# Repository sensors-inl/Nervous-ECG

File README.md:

<p align="center">
    <h1 align="center">Nervous ECG Sensor</h1>
</p>

<p align="center">

</p>

## Table of Contents

- [Table of Contents](#table-of-contents)
- [Overview](#overview)
- [Features](#features)
- [Instructions](#instructions)
- [Releases](#releases)
- [Contributing](#contributing)
- [License](#license)
- [Acknowledgments](#acknowledgments)
- [Contact](#contact)

---

## Overview

The **Nervous** project is an initiative based on open-hardware and open-source principles, aimed at providing wearable sensors and software for analyzing the Autonomic Nervous System (ANS) activity.

The **Nervous ECG** project is part of the **[Nervous Toolkit](https://github.com/sensors-inl/Nervous-Toolkit)** and includes hardware design files and firmware source files for creating an electrocardiogram (ECG) sensor to measure the ECG signal **from the hands or forearms**.
The device is wireless and transmits the collected data via Bluetooth Low Energy.

---

## Features

This project is actually a collection of three sub-projects for the sensor design, located in the following directories:

[hardware](./hardware/): This folder contains ECAD files for producing PCBs and assembling circuits for a wireless wrist-worn ECG sensor.
A archive (.zip) containing the design and manufacturing/assembly files for the sensor is available in the releases of this project.

[firmware](./firmware/): This folder contains source files to build binaries for programming the microcontroller.
Precompiled binaries are also provided in the releases of this project.

[web-app](./web-app/): While the sensor is primarily designed to work with the [```nervous-sensors```](https://github.com/sensors-inl/Nervous-Sensors) Python package included in the Nervous Toolkit, a standalone web application is provided for simplified use of the sensor.
It offers sensor control, real-time data visualization, and recording features.
Pre-built executables for both Microsoft Windows and Linux are also available in the releases of this project.

---

## Instructions

Detailed instructions are provided in each subdirectory for manufacturing, programming, and using the sensor.

---

## Releases

Each [release](https://github.com/sensors-inl/Nervous-ECG/releases/latest) contains built firmware and application binaries as well as an archive of ECAD files.

---

## Contributing

Contributions are what make the open-source community such a great place to learn, inspire, and create. Any contributions you make are greatly appreciated. You can open an issue to report a bug, request a feature, or submit a pull request.

---

## License

This project, along with the entire Nervous initiative, is licensed under the [MIT License](https://opensource.org/licenses/MIT). For more details, see the [License](LICENSE.md) file.

---

## Acknowledgments

The main contributors to this project are Bertrand Massot, Matthieu Mesnage, and Hugo Buy from INSA Lyon, CNRS, INL UMR 5270, Villeurbanne, France.

This work was supported by the **French National Research Agency (ANR)** under grant **ANR-22-CE31-0023-03 RENFORCE**.

---

## Contact

[bertrand.massot@insa-lyon.fr](mailto:bertrand.massot@insa-lyon.fr)

---

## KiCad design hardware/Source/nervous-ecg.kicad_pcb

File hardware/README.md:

<p align="center">
    <h1 align="center">Nervous ECG Hardware</h1>
</p>

<p align="center">

</p>

## Table of Contents

- [Table of Contents](#table-of-contents)
- [Overview](#overview)
- [Hardware features](#hardware-features)
- [Manufacturing and assembling](#manufacturing-and-assembling)
  - [PCB properties for manufacturing](#pcb-properties-for-manufacturing)
- [Modification](#modification)
- [Casing](#casing)
- [Note on cables and electrodes placement to reduce signal noise](#note-on-cables-and-electrodes-placement-to-reduce-signal-noise)
- [Release](#release)

---

## Overview

This folder contains ECAD files for the production of PCBs and assembly of circuits for the Nervous ECG sensor.
The printed circuit board was designed using the open source electronics design automation suite [KiCad EDA](https://www.kicad.org/) v9.0.0

Originally designed for measuring heart rate via electrodes placed on the forearms or hands, this sensor utilizes the AD8232 along with passive components, as described in the "EXERCISE APPLICATION: HEART RATE MEASURED AT THE HANDS" section on page 27 of the [datasheet](<https://www.analog.com/media/en/technical-documentation/data-sheets/ad8232.pdf>).
You can modify this configuration for different applications and electrode placements.

The microcontroller used is the nRF52840 (Nordic Semiconductor) within the ISP1807 System-in-Package (Insight SiP).

---

## Hardware features

- USB-C connector for charging the battery
- Embedded LiPo battery charger and I2C fuel gauge
- On/Off SPST button (enables/disables the voltage regulator)
- RGB status LED
- AD8232 ECG AFE with a 7 Hz - 24 Hz bandpass filter (56 dB @ 13 Hz) and RLD
- nRF52840 (ISP1807) with Bluetooth Low Energy

---

## Manufacturing and assembling

The following files are available in the `Export` folder:

- **Export/Manufacturing**: contains Gerber (.gbr) and drill files (.drl)
- **Export/Assembly**: contains assembly drawing (.pdf), pick and place files (.pos), and BOM (.csv)

---

### PCB properties for manufacturing

Some PCB manufacturers may require the following properties. The table below summarizes the principal PCB properties:

| Property                    | Value              |
| --------------------------- | ------------------ |
| Dimensions                  | 21.5 mm x 33.5 mm  |
| Number of layers            | 2                  |
| Minimal insulation width    | 0.150 mm           |
| Minimal trace width         | 0.150 mm           |
| Minimal hole size           | 0.200 mm           |

---

## Modification

The `Source` folder contains the original KiCad project, created using KiCad version 7.0.8.

---

## Casing

Several 3D models are available for producing a casing for the electronics. STEP and STL files are located in the `Casing` folder:

- **casing_top** and **casing_bottom** are two parts that assemble together with two M2 screws, where the PCB and a 150 mAh LiPo battery fit. A specially designed battery compartment ensures that it does not overlap with the antenna of the ISAP1807 chip located on the longitudinal edge of the PCB. The design of the bottom part includes handles for wrist attachment.
- **casing_bottom_controller** is a modified version of the bottom part, designed to mount the electronics circuit and battery onto a Valve Index controller for ECG assessment during virtual environment sessions.

---

## Note on cables and electrodes placement to reduce signal noise

This sensor is designed to capture ECG signals under various conditions while minimizing discomfort. To achieve this, it uses high gain to support electrode placement on the hands or forearms, where signal strength is typically lower. However, this placement also amplifies sensitivity to motion artifacts, which can affect heart rate accuracy.

To minimize these artifacts, we recommend using solid gel electrodes, such as the 3M&reg; 2650. The sensor features a simple 2.54 mm, 3-way header for custom electrode connections. It is recommended to use short cables for the two electrodes near the device (RLD and RA), and a longer cable for the third electrode on the opposite arm (LA). The cables are designed with female crimp terminals at the sensor end and snap adapters at the electrode end. We recommend using cables with low triboelectric effect, such as Belden 9239 Low Noise Coaxial cable. To reduce noise from connector friction, securely hold the electrodes and cables near the electrodes with medical tape.

---

## Release

The entire folder is provided as an archive (`Nervous-ECG-hardware-vX.X.X.zip`) in the [releases](https://github.com/sensors-inl/Nervous-ECG/releases/latest) of this project.

---

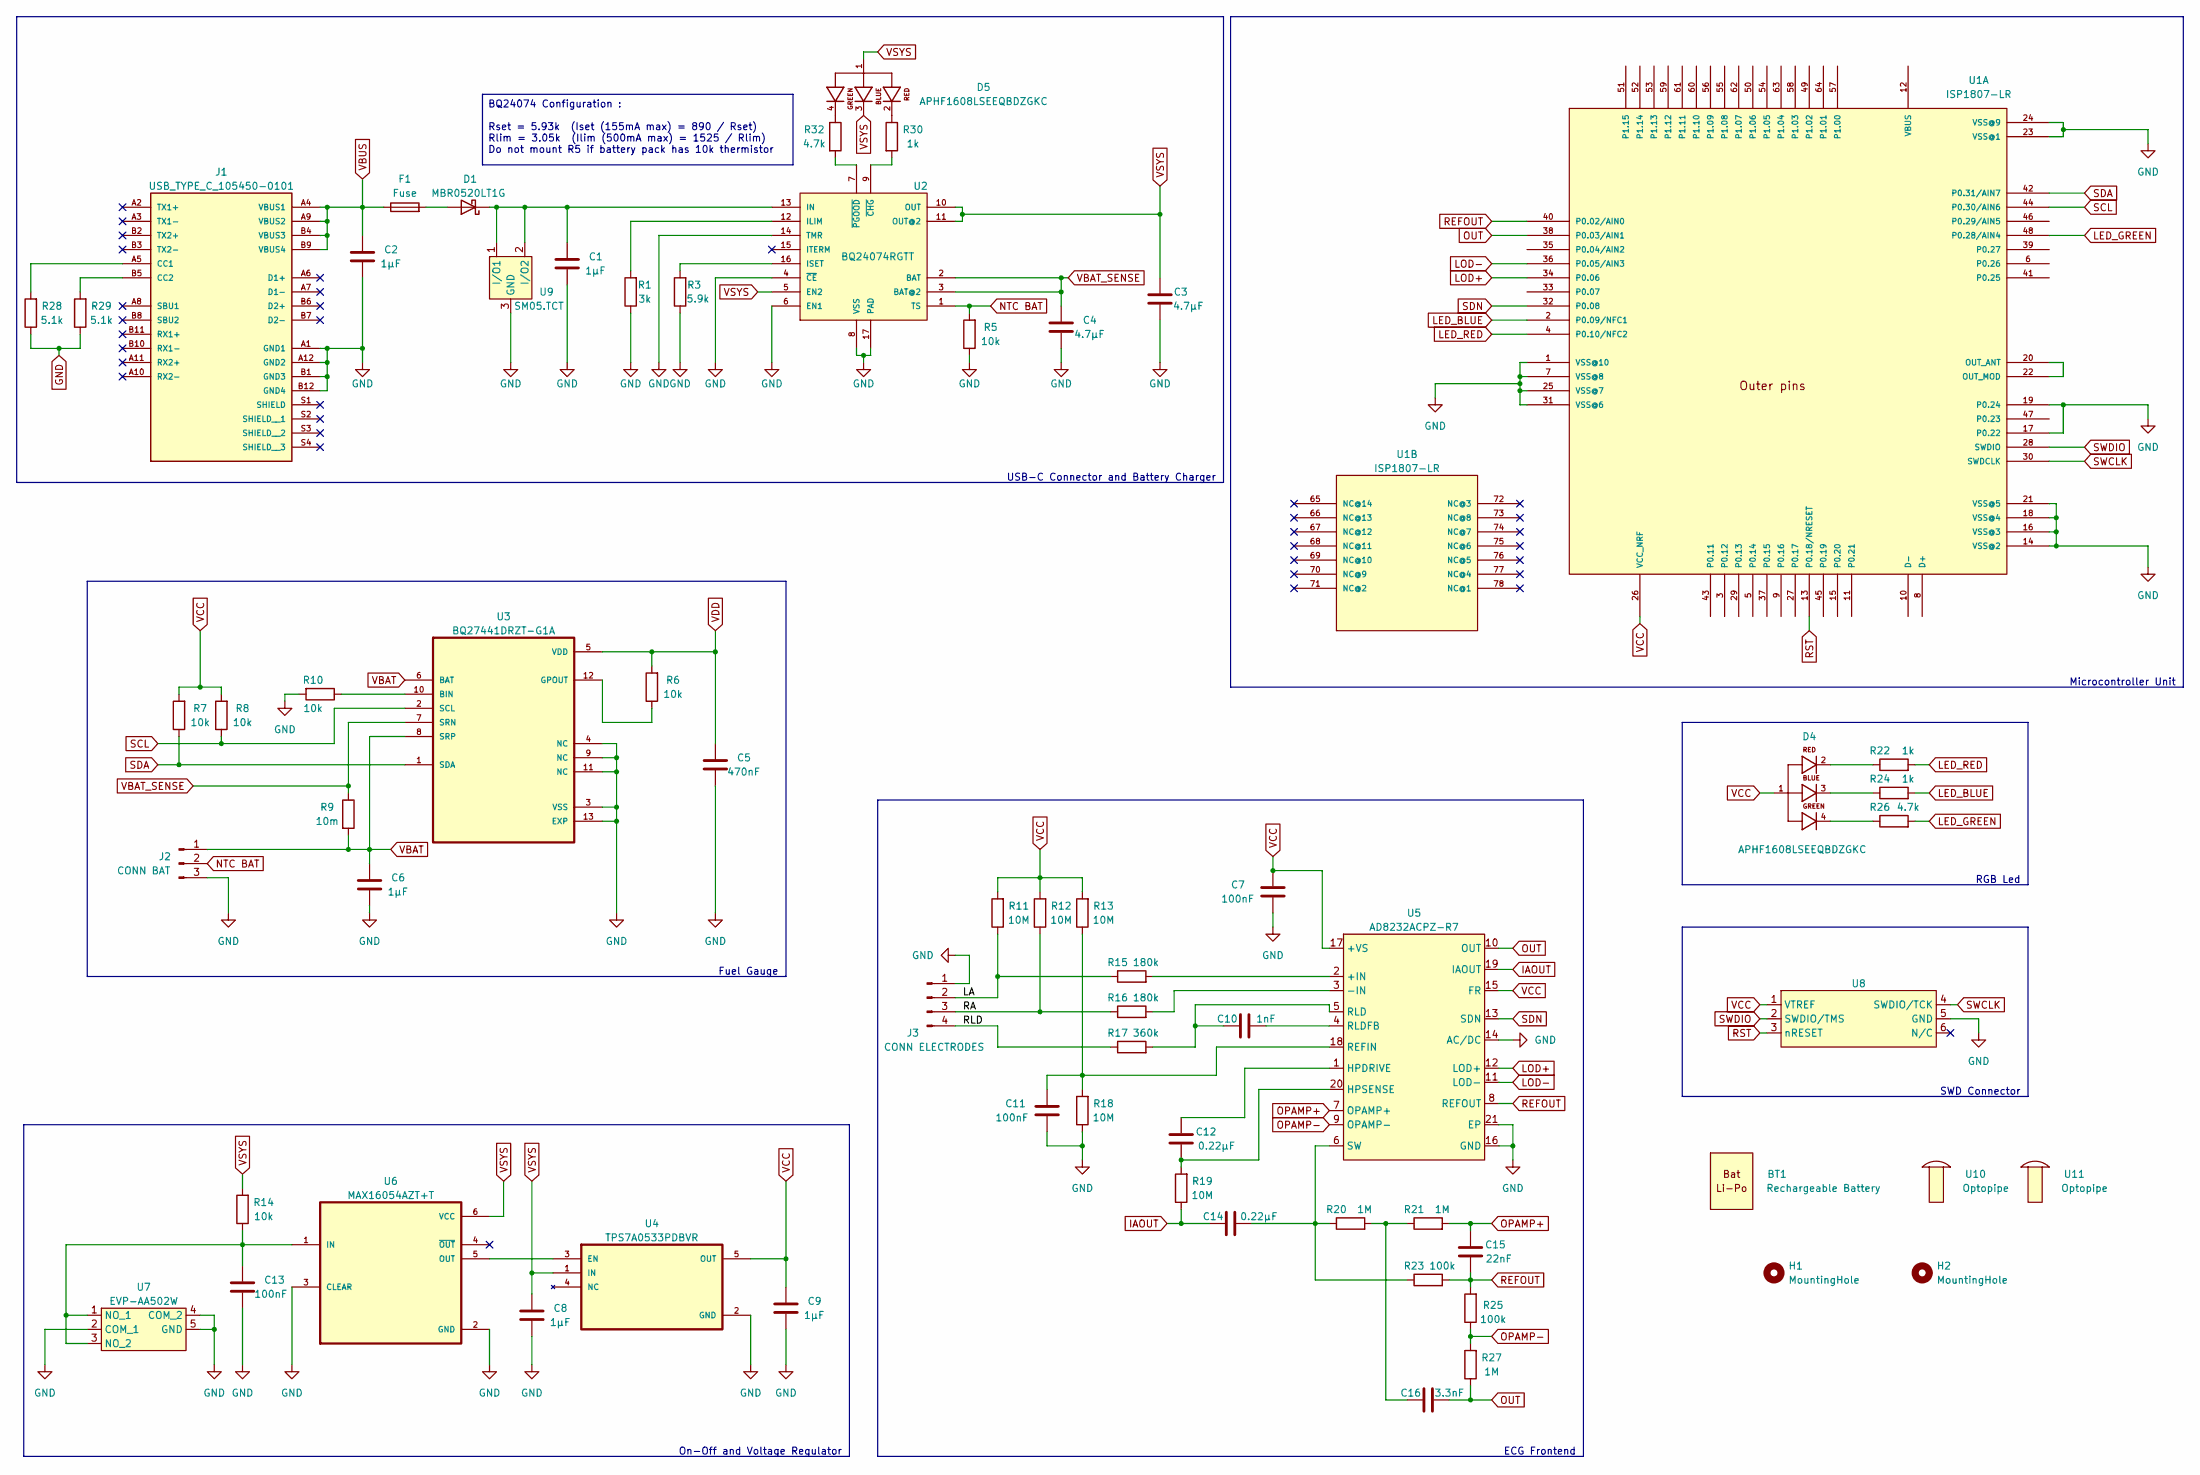
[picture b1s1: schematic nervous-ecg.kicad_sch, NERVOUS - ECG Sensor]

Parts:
BT1: BATT LI-PO 3.7V 165MAH; Manufacturer Part Number LP-402025-1S-3
C1, C2, C6, C8, C9: CAP CER 1UF 10V X5R 0402; C_0402_1005Metric; Manufacturer Part Number CC0402KRX5R6BB105
C3, C4: CAP CER 4.7UF 6.3V X5R 0402; C_0402_1005Metric; Manufacturer Part Number CC0402KRX5R5BB475
C5: CAP CER 0.47UF 10V X5R 0402; C_0402_1005Metric; Manufacturer Part Number CC0402KRX5R6BB474
C7, C11, C13: CAP CER 0.1UF 16V X7R 0402; C_0402_1005Metric; Manufacturer Part Number CC0402JRX7R7BB104
C10: CAP CER 1000PF 50V X7R 0402; C_0402_1005Metric; Manufacturer Part Number CC0402KRX7R9BB102
C12, C14: CAP CER 0.22UF 10V X5R 0402; C_0402_1005Metric; Manufacturer Part Number CC0402KRX5R6BB224
C15: CAP CER 22000PF 16V X7R 0402; C_0402_1005Metric; Manufacturer Part Number CC0402KRX7R7BB223
C16: CAP CER 3300PF 50V X7R 0402; C_0402_1005Metric; Manufacturer Part Number CC0402KRX7R9BB332
D1: DIODE SCHOTTKY 20V 500MA SOD123; D_SOD-123; Manufacturer Part Number STPS0520Z
D4, D5: LED RGB CLEAR 4SMD; APHF1608LSEEQBDZGKC; Manufacturer Part Number APHF1608LSEEQBDZGKC
F1: PTC RESET FUSE 16V 500MA 1210; Fuse_1210_3225Metric; Manufacturer Part Number 0ZCH0050FF2G
H1, H2: MountingHole; MountingHole_2mm
J1: CONN RCP USB3.1 TYPEC 24P SMD RA; USB_TYPE_C_105450-0101; Manufacturer Part Number 105450-0101
J2: MOLEX 53048-0310; CONN_BAT_53048-0310; Manufacturer Part Number 53048-0310
J3: CONN HEADER R/A 4POS 2.54MM; CONN_ELECTRODE; Manufacturer Part Number 77315-118-04LF
R1: RES SMD 3K OHM 1% 1/16W 0402; R_0402_1005Metric; Manufacturer Part Number AC0402FR-073KL
R3: RES 5.9K OHM 1% 1/16W 0402; R_0402_1005Metric; Manufacturer Part Number RC0402FR-075K9L
R5, R6, R7, R8, R10, R14: RES 10K OHM 1% 1/16W 0402; R_0402_1005Metric; Manufacturer Part Number RC0402FR-0710KL
R9: RES 0.01 OHM 1% 1/10W 0603; R_0603_1608Metric; Manufacturer Part Number RL0603FR-070R01L
R11, R12, R13, R18, R19: RES SMD 10M OHM 1% 1/16W 0402; R_0402_1005Metric; Manufacturer Part Number RC0402FR-0710ML
R15, R16: RES SMD 180K OHM 1% 1/10W 0402; R_0402_1005Metric; Manufacturer Part Number ERJ-H2RF1803X
R17: RES SMD 360K OHM 1% 1/16W 0402; R_0402_1005Metric; Manufacturer Part Number RC0402FR-07360KL
R20, R21, R27: RES SMD 1M OHM 1% 1/16W 0402; R_0402_1005Metric; Manufacturer Part Number RC0402FR-071ML
R22, R24, R30: RES 1K OHM 1% 1/16W 0402; R_0402_1005Metric; Manufacturer Part Number RC0402FR-071KL
R23, R25: RES 100K OHM 1% 1/16W 0402; R_0402_1005Metric; Manufacturer Part Number RC0402FR-07100KL
R26, R32: RES 4.7K OHM 1% 1/16W 0402; R_0402_1005Metric; Manufacturer Part Number RC0402FR-074K7L
R28: RES 5.1K OHM 0.5% 1/10W 0402; R_0402_1005Metric; Manufacturer Part Number ERJ-U2RD5101X
R29: RES 5.1K OHM 0.5% 1/10W 0402; C_0402_1005Metric; Manufacturer Part Number ERJ-U2RD5101X
U1: RF TXRX MODULE BT TRACE ANT SMD; ISP1807-LR; Manufacturer Part Number ISP1807-LR-RS
U2: IC BATT CHG LI-ION 1CELL 16QFN; BQ24074RGTx; Manufacturer Part Number BQ24074RGTT
U3: IC BATT FUEL GAUGE LICOO2 12SON; BQ27441DRZR-G1A; Manufacturer Part Number BQ27441DRZR-G1A
U4: IC REG LINEAR 3.3V 200MA SOT23-5; TPS7A0533PDBVR; Manufacturer Part Number TPS7A0533PDBVR
U5: IC ECG FRONT END 20LFCSP; AD8232ACPZ-R7; Manufacturer Part Number AD8232ACPZ-R7
U6: IC INTFACE SPECIALIZED TSOT23-6; MAX16054AZT+T; Manufacturer Part Number MAX16054AZT+T
U7: SWITCH TACTILE SPST-NO 0.02A 15V; EVP-AA502W; Manufacturer Part Number EVP-AA502W
U8: TC2030-MCP-NL
U9: TVS Diode WE-TVS-Standard, VRWM=5.0V; SM05.TCT; Manufacturer Part Number SM05.TCT
U10, U11: LIGHTPIPE PNL MT CONVEX 0.250"; Manufacturer Part Number 515-1302-0250F

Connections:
/LA: J3.2, R11.1, R15.1
/RA: J3.3, R12.1, R16.1
/RLD: J3.4, R17.1
GND: C1.2, C2.2, C3.1, C4.2, C5.2, C6.2, C7.2, C8.2, C9.2, C11.2, C13.2, J1.A1 (GND1), J1.A12 (GND2), J1.B1 (GND3), J1.B12 (GND4), J2.3, J3.1, R1.1, R3.1, R5.1, R10.2, R18.1, R28.1, R29.1, U1.1 (VSS@10), U1.7 (VSS@8), U1.14 (VSS@2), U1.16 (VSS@3), U1.17 (P0.22), U1.18 (VSS@4), U1.19 (P0.24), U1.21 (VSS@5), U1.23 (VSS@1), U1.24 (VSS@9), U1.25 (VSS@7), U1.31 (VSS@6), U2.4 (~CE), U2.6 (EN1), U2.8 (VSS), U2.14 (TMR), U2.17 (PAD), U3.3 (VSS), U3.4 (NC), U3.9 (NC), U3.11 (NC), U3.13 (EXP), U4.2 (GND), U5.14 (AC/DC), U5.16 (GND), U5.21 (EP), U6.2 (GND), U6.3 (CLEAR), U7.2 (COM_1), U7.4 (COM_2), U7.5 (GND), U8.5 (GND), U9.3 (GND)
IAOUT: C14.2, R19.1, U5.19 (IAOUT)
LED_BLUE: R24.2, U1.2 (P0.09/NFC1)
LED_GREEN: R26.2, U1.48 (P0.28/AIN4)
LED_RED: R22.2, U1.4 (P0.10/NFC2)
LOD+: U1.34 (P0.06), U5.12 (LOD+)
LOD-: U1.36 (P0.05/AIN3), U5.11 (LOD-)
NTC BAT: J2.2, R5.2, U2.1 (TS)
unnamed: C16.2, R20.2, R21.1
unnamed: D1.2 (A), F1.2
unnamed: C1.1, D1.1 (K), U2.13 (IN), U9.1 (I/O1), U9.2 (I/O2)
unnamed: D4.2, R22.1
unnamed: D4.3, R24.1
unnamed: D4.4, R26.1
unnamed: D5.2, R30.1
unnamed: D5.4, R32.1
unnamed: J1.A5 (CC1), R28.2
unnamed: J1.B5 (CC2), R29.2
unnamed: U1.20 (OUT_ANT), U1.22 (OUT_MOD)
unnamed: R1.2, U2.12 (ILIM)
unnamed: R3.2, U2.16 (ISET)
unnamed: R30.2, U2.9 (~CHG)
unnamed: R32.2, U2.7 (~PGOOD)
unnamed: R10.1, U3.10 (BIN)
unnamed: R6.1, U3.12 (GPOUT)
unnamed: U4.3 (EN), U6.5 (OUT)
unnamed: R15.2, U5.2 (+IN)
unnamed: R16.2, U5.3 (-IN)
unnamed: C12.1, U5.1 (HPDRIVE)
unnamed: C12.2, R19.2, U5.20 (HPSENSE)
unnamed: C11.1, R13.1, R18.2, U5.18 (REFIN)
unnamed: C10.2, R17.2, U5.5 (RLD)
unnamed: C10.1, U5.4 (RLDFB)
unnamed: C14.1, R20.1, R23.1, U5.6 (SW)
unnamed: C13.1, R14.1, U6.1 (IN), U7.1 (NO_1), U7.3 (NO_2)
OPAMP+: C15.1, R21.2, U5.7 (OPAMP+)
OPAMP-: R25.1, R27.2, U5.9 (OPAMP-)
OUT: C16.1, R27.1, U1.38 (P0.03/AIN1), U5.10 (OUT)
REFOUT: C15.2, R23.2, R25.2, U1.40 (P0.02/AIN0), U5.8 (REFOUT)
RST: U1.13 (P0.18/NRESET), U8.3 (nRESET)
SCL: R8.1, U1.44 (P0.30/AIN6), U3.2 (SCL)
SDA: R7.1, U1.42 (P0.31/AIN7), U3.1 (SDA)
SDN: U1.32 (P0.08), U5.13 (SDN)
SWCLK: U1.30 (SWDCLK), U8.4 (SWDIO/TCK)
SWDIO: U1.28 (SWDIO), U8.2 (SWDIO/TMS)
VBAT: C6.1, J2.1, R9.2, U3.6 (BAT), U3.8 (SRP)
VBAT_SENSE: C4.1, R9.1, U2.2 (BAT), U2.3 (BAT@2), U3.7 (SRN)
VBUS: C2.1, F1.1, J1.A4 (VBUS1), J1.A9 (VBUS2), J1.B4 (VBUS3), J1.B9 (VBUS4)
VCC: C7.1, C9.1, D4.1, R7.2, R8.2, R11.2, R12.2, R13.2, U1.26 (VCC_NRF), U4.5 (OUT), U5.15 (FR), U5.17 (+VS), U8.1 (VTREF)
VDD: C5.1, R6.2, U3.5 (VDD)
VSYS: C3.2, C8.1, D5.1, D5.3, R14.2, U2.5 (EN2), U2.10 (OUT), U2.11 (OUT@2), U4.1 (IN), U6.6 (VCC)

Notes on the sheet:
RGB Led
Fuel Gauge
USB-C Connector and Battery Charger
ECG Frontend
SWD Connector
Microcontroller Unit
On-Off and Voltage Regulator
BQ24074 Configuration : Rset = 5.93k (Iset (155mA max) = 890 / Rset) Rlim = 3.05k (Ilim (500mA max) = 1525 / Rlim) Do not mount R5 if battery pack has 10k thermistor

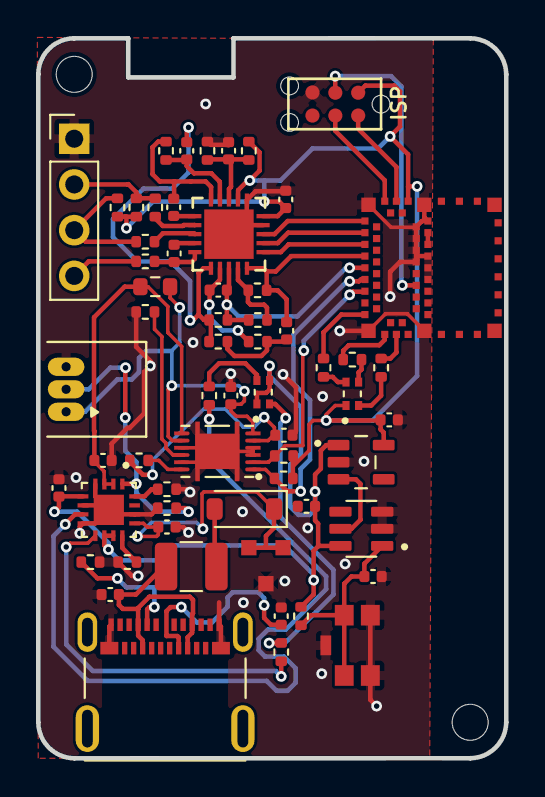
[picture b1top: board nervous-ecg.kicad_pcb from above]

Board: 2 copper layers, 26.0 x 40.0 mm, 63 parts (0 on the bottom side), 54 nets.

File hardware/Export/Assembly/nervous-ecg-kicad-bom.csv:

Id;Quantity;Designator;Description;Manufacturer;Manufacturer Part Number;Supplier;Supplier Part Number
1;1;BT1;BATT LI-PO 3.7V 165MAH ;BAK TECHNOLOGY;LP-402025-1S-3;FARNELL;2077885
2;5;C1, C2, C6, C8, C9;CAP CER 1UF 10V X5R 0402;Yageo;CC0402KRX5R6BB105;Farnell;1458896
3;2;C3, C4;CAP CER 4.7UF 6.3V X5R 0402;Yageo;CC0402KRX5R5BB475;Farnell;3369135
4;1;C5;CAP CER 0.47UF 10V X5R 0402;Yageo;CC0402KRX5R6BB474;Farnell;3369138
5;3;C7, C11, C13;CAP CER 0.1UF 16V X7R 0402;Yageo;CC0402JRX7R7BB104;Farnell;3369125
6;1;C10;CAP CER 1000PF 50V X7R 0402;Yageo;CC0402KRX7R9BB102;Farnell;3019380
7;2;C12, C14;CAP CER 0.22UF 10V X5R 0402;Yageo;CC0402KRX5R6BB224;Farnell;9402055
8;1;C15;CAP CER 22000PF 16V X7R 0402;Yageo;CC0402KRX7R7BB223;Farnell;3019299
9;1;C16;CAP CER 3300PF 50V X7R 0402;Yageo;CC0402KRX7R9BB332;Farnell;3873402
10;1;D1;DIODE SCHOTTKY 20V 500MA SOD123;STMicroelectronics;STPS0520Z;FARNELL;1467545
11;2;D4, D5;LED RGB CLEAR 4SMD;KINGBRIGHT;APHF1608LSEEQBDZGKC;DIGIKEY;754-2143-1-ND
12;1;F1;PTC RESET FUSE 16V 500MA 1210;BEL;0ZCH0050FF2G;Farnell;2848519
13;1;J1;CONN RCP USB3.1 TYPEC 24P SMD RA;MOLEX;105450-0101;FARNELL;2524076
14;1;J2;MOLEX 53048-0310;MOLEX;53048-0310;FARNELL;9732918
15;1;J4;CONN HEADER R/A 4POS 2.54MM;AMPHENOL COMMUNICATIONS SOLUTIONS;77315-118-04LF;FARNELL;3728851
16;1;R1;RES SMD 3K OHM 1% 1/16W 0402;Yageo;AC0402FR-073KL;Farnell;3951323
17;1;R3;RES 5.9K OHM 1% 1/16W 0402;Yageo;RC0402FR-075K9L;Farnell;3951010
18;6;R5, R6, R7, R8, R10, R14;RES 10K OHM 1% 1/16W 0402;Yageo;RC0402FR-0710KL;Farnell;9239359
19;1;R9;RES 0.01 OHM 1% 1/10W 0603;Yageo;RL0603FR-070R01L;Farnell;8067767
20;5;R11, R12, R13, R18, R19;RES SMD 10M OHM 1% 1/16W 0402;Yageo;RC0402FR-0710ML;Farnell;1458733
21;2;R15, R16;RES SMD 180K OHM 1% 1/10W 0402;Panasonic;ERJ-H2RF1803X;Farnell;3644222
22;1;R17;RES SMD 360K OHM 1% 1/16W 0402;Yageo;RC0402FR-07360KL;Digi-Key;311-360KLRCT-ND
23;3;R20, R21, R27;RES SMD 1M OHM 1% 1/16W 0402;Yageo;RC0402FR-071ML;Farnell;9239588
24;3;R22, R24, R30;RES 1K OHM 1% 1/16W 0402;Yageo;RC0402FR-071KL;Farnell;9239235
25;2;R23, R25;RES 100K OHM 1% 1/16W 0402;Yageo;RC0402FR-07100KL;Farnell;9239472
26;2;R26, R32;RES 4.7K OHM 1% 1/16W 0402;Yageo;RC0402FR-074K7L;Farnell;9239316
27;1;R28;RES 5.1K OHM 0.5% 1/10W 0402;PANASONIC;ERJ-U2RD5101X;FARNELL;3516311
28;1;R29;RES 5.1K OHM 0.5% 1/10W 0402;PANASONIC;ERJ-U2RD5101X;FARNELL;3516311
29;1;U1;RF TXRX MODULE BT TRACE ANT SMD;INSIGHT SIP;ISP1807-LR-RS;DIGIKEY;1786-1019-1-ND
30;1;U2;IC BATT CHG LI-ION 1CELL 16QFN;TEXAS INSTRUMENTS;BQ24074RGTT;FARNELL;3123775
31;1;U3;IC BATT FUEL GAUGE LICOO2 12SON;TEXAS INSTRUMENTS;BQ27441DRZR-G1A;FARNELL;3123775
32;1;U4;IC REG LINEAR 3.3V 200MA SOT23-5;TEXAS INSTRUMENTS;TPS7A0533PDBVR;DIGIKEY;296-TPS7A0533PDBVRDKR-ND
33;1;U5;IC ECG FRONT END 20LFCSP;Analog Devices;AD8232ACPZ-R7;Farnell;4029748
34;1;U6;IC INTFACE SPECIALIZED TSOT23-6;ANALOG DEVICES;MAX16054AZT+T;FARNELL;2515822
35;1;U7;SWITCH TACTILE SPST-NO 0.02A 15V;PANASONIC;EVP-AA502W;FARNELL;2831733
36;1;U9;TVS Diode WE-TVS-Standard, VRWM=5.0V;SEMTECH;SM05.TCT;Farnell;1456392
37;1;U10;"LIGHTPIPE PNL MT CONVEX 0.250""";DIALIGHT;515-1302-0250F;FARNELL;3775816

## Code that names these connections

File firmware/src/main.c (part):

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K_TIMER_DEFINE(rgb_led_timer, rgb_led_timer_handler, NULL);

/* RGB Led pins */
static const struct gpio_dt_spec led_red_pin    = GPIO_DT_SPEC_GET_BY_IDX(DT_PATH(zephyr_user), led_rgb_gpios, 0);
static const struct gpio_dt_spec led_green_pin  = GPIO_DT_SPEC_GET_BY_IDX(DT_PATH(zephyr_user), led_rgb_gpios, 1);
static const struct gpio_dt_spec led_blue_pin   = GPIO_DT_SPEC_GET_BY_IDX(DT_PATH(zephyr_user), led_rgb_gpios, 2);

/* Fuel gauge device */
static const struct device *fuel_gauge = DEVICE_DT_GET(DT_NODELABEL(bq27441));
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/* Init RGB gpios */
static void rgb_led_init(void)
{
    gpio_pin_configure_dt(&led_red_pin,   GPIO_OUTPUT_INACTIVE);
    gpio_pin_configure_dt(&led_green_pin, GPIO_OUTPUT_INACTIVE);
    gpio_pin_configure_dt(&led_blue_pin,  GPIO_OUTPUT_INACTIVE);
}

/* Set RGB state */
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{
    /* if led was blinking we need to be sure that timer is stopped */
    k_timer_stop(&rgb_led_timer);
    gpio_pin_set_dt(&led_red_pin,   red);
    gpio_pin_set_dt(&led_green_pin, green);
    gpio_pin_set_dt(&led_blue_pin,  blue);
}

/* Start the RGB led blinking timer */
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/* RGB led blinking timer callback */
static void rgb_led_timer_handler(struct k_timer *timer)
{
    gpio_pin_toggle_dt(&led_blue_pin);
}

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
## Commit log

2024-11-20 chore: replace Fusion 360 archive files by .step files
2024-11-20 feat: add ECAD files archive to release
2024-11-20 doc: improve documentation
2024-11-25 fix: wait for initial release creation before launching jobs
2024-11-27 doc: update documentation
2025-03-20 fix: project naming
2025-03-20 fix: update csv header and remove space between columns
2025-03-20 fix : readjustment of decoupling capacitors positioning
2025-03-20 feat: bump to kicad 9.0.0
2025-03-20 fix: align web-app and python csv headers
2025-03-20 doc: update KiCad version
2025-03-20 fix: update board revision
2025-03-20 fix: export files
2025-03-21 fix: add device name in csv file

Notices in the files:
README.md:
License: MIT
hardware/Source/nervous-ecg.kicad_pcb:
Copyright (c) 2024 INSA Lyon, CNRS, INL UMR5270
License : MIT License
